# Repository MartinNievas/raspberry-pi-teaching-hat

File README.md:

# raspberry-pi-teaching-hat

## Pinout

## Programa de ejemplo
Un programa de ejemplo se encuentra en la carpeta lib/

Ejecutar:

```bash
gcc ejemplo.c && sudo ./a.out
```
Nota: sudo es necesario para acceder al pinout.

---
Para más información ir a la [Wiki](https://github.com/MartinNievas/raspberry-pi-teaching-hat/wiki)
---

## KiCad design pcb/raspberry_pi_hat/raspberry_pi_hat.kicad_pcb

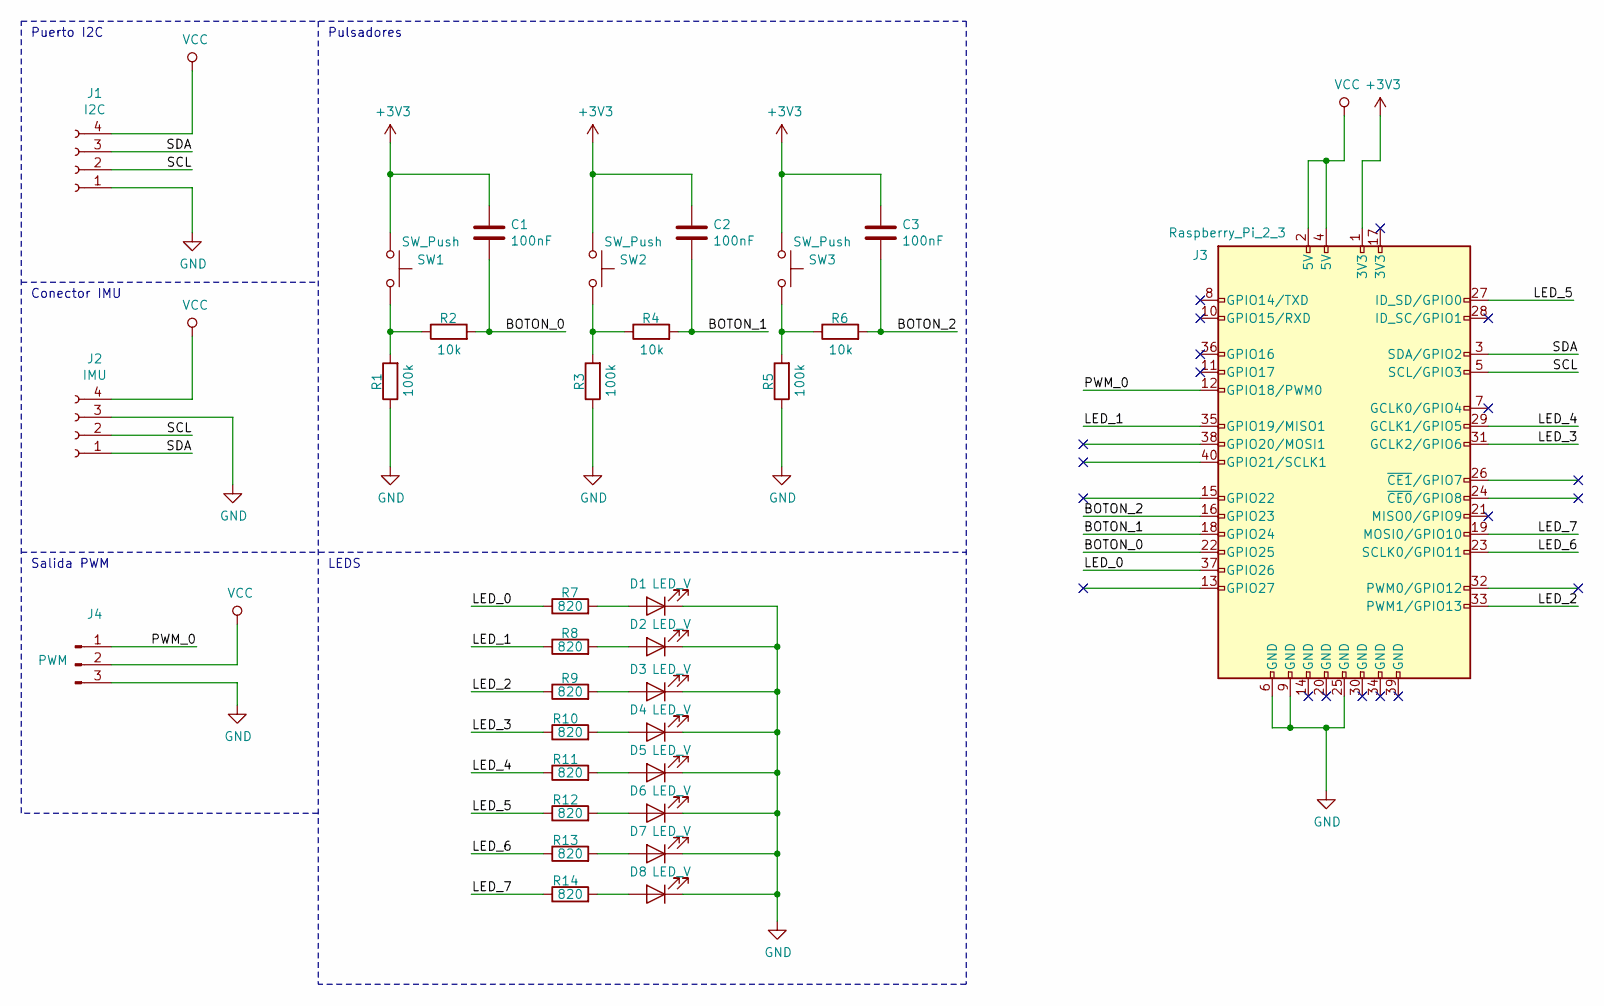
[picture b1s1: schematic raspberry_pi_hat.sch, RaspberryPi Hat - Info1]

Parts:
C1, C2, C3: 100nF; cnp_6mm_disc
D1, D2, D3, D4, D5, D6, D7, D8: LED_V; LED_D5.0mm
J1: I2C; PinHeader_1x04_P2.54mm_Vertical
J2: IMU; PinHeader_1x04_P2.54mm_Vertical
J3: Raspberry_Pi_2_3; Pin_Header_Straight_2x20
J4: PWM; PinHeader_1x03_P2.54mm_Horizontal
R1, R3, R5: 100k; R_BIG_Axial_DIN0207
R2, R4, R6: 10k; R_BIG_Axial_DIN0207
R7, R8, R9, R10, R11, R12, R13, R14: 820; R_BIG_Axial_DIN0207
SW1, SW2, SW3: SW_Push; SW_PUSH_6mm

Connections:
+3V3: C1.1, C2.1, C3.1, J3.1 (3V3), SW1.1, SW2.1, SW3.1
/BOTON_0: C1.2, J3.22 (GPIO25), R2.2
/BOTON_1: C2.2, J3.18 (GPIO24), R4.2
/BOTON_2: C3.2, J3.16 (GPIO23), R6.2
/LED_0: J3.37 (GPIO26), R7.1
/LED_1: J3.35 (GPIO19/MISO1), R8.1
/LED_2: J3.33 (PWM1/GPIO13), R9.1
/LED_3: J3.31 (GCLK2/GPIO6), R10.1
/LED_4: J3.29 (GCLK1/GPIO5), R11.1
/LED_5: J3.27 (ID_SD/GPIO0), R12.1
/LED_6: J3.23 (SCLK0/GPIO11), R13.1
/LED_7: J3.19 (MOSI0/GPIO10), R14.1
/PWM_0: J3.12 (GPIO18/PWM0), J4.1
/SCL: J1.2, J2.2, J3.5 (SCL/GPIO3)
/SDA: J1.3, J2.1, J3.3 (SDA/GPIO2)
GND: D1.1 (K), D2.1 (K), D3.1 (K), D4.1 (K), D5.1 (K), D6.1 (K), D7.1 (K), D8.1 (K), J1.1, J2.3, J3.6 (GND), J3.9 (GND), J3.25 (GND), J4.3, R1.1, R3.1, R5.1
unnamed: D1.2 (A), R7.2
unnamed: D2.2 (A), R8.2
unnamed: D3.2 (A), R9.2
unnamed: D4.2 (A), R10.2
unnamed: D5.2 (A), R11.2
unnamed: D6.2 (A), R12.2
unnamed: D7.2 (A), R13.2
unnamed: D8.2 (A), R14.2
unnamed: R1.2, R2.1, SW1.2
unnamed: R3.2, R4.1, SW2.2
unnamed: R5.2, R6.1, SW3.2
VCC: J1.4, J2.4, J3.2 (5V), J3.4 (5V), J4.2

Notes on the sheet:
Puerto I2C
Conector IMU
Salida PWM
LEDS
Pulsadores

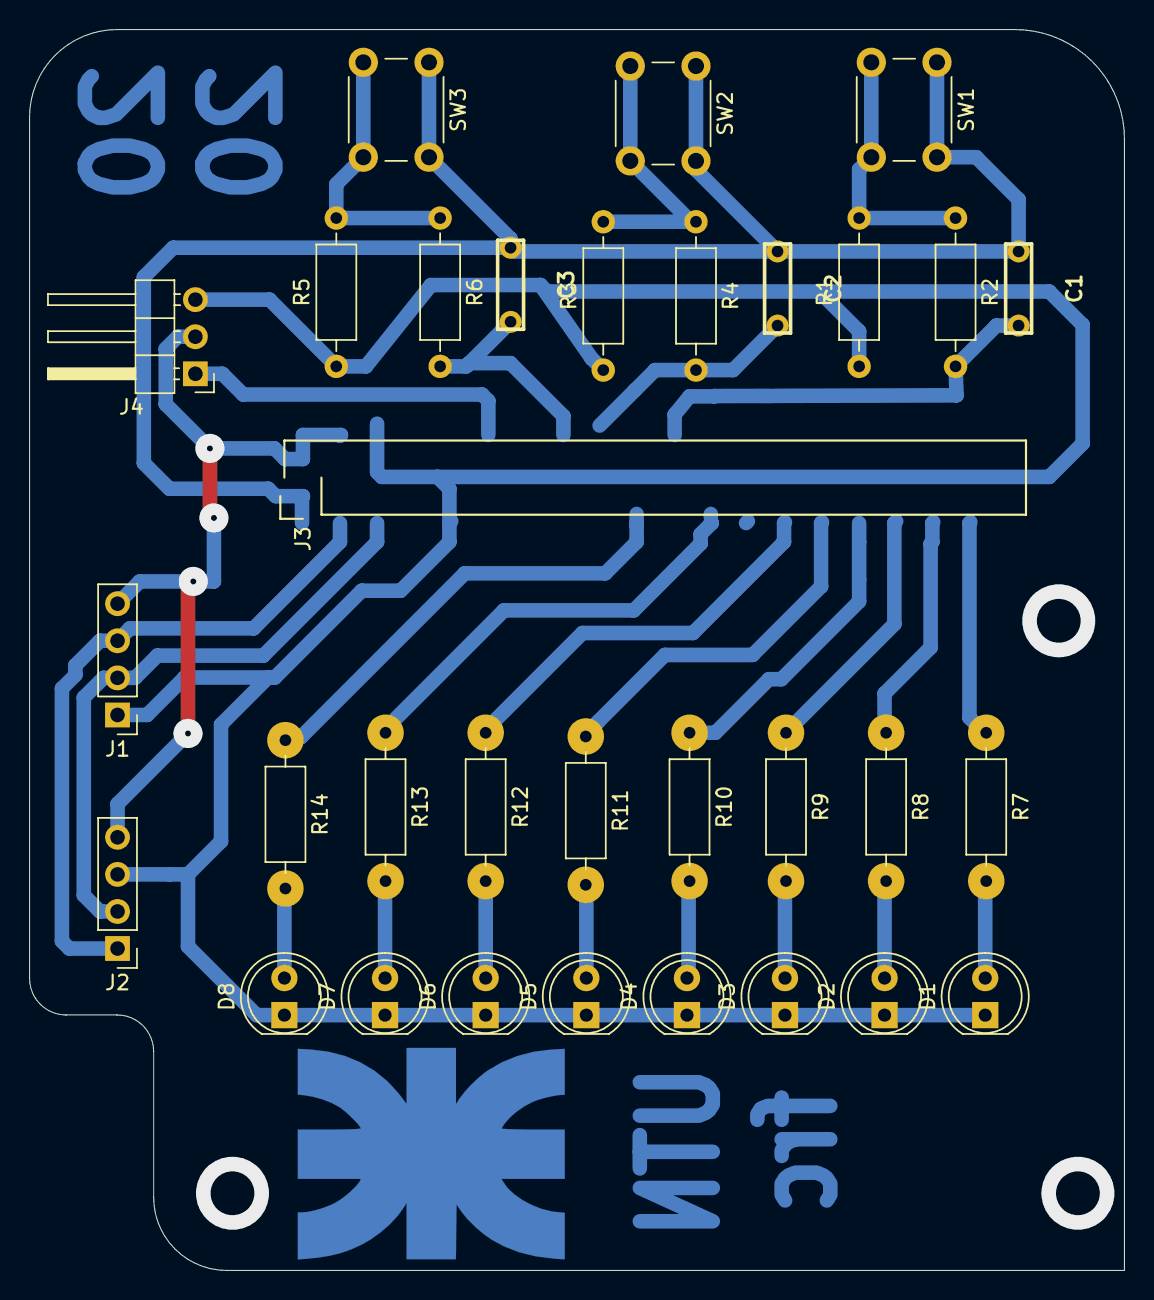
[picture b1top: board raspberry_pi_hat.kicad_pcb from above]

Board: 2 copper layers, 75.0 x 85.0 mm, 32 parts (0 on the bottom side), 28 nets.

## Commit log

2019-07-02 Add gitignore for KiCad files
2020-02-26 Agrega versión 0.1 del hat
2020-02-26 Agrega renders de la placa
2020-02-26 Agrega render al README
2020-03-10 Agrega modificaciones en el tamaño del PCB
2020-03-14 Agrega modelos para el case
2020-03-14 Agrega render de la placa
2020-03-14 Agrega links a los modelos stl
2020-03-14 Agrega imágenes de la placa nueva
2020-03-14 Corrige una esquina del case
2020-03-19 Agrega documentación y pinout
2020-03-19 Agrega biblioteca EasyPIO.h y programa de ejemplo
2020-03-22 Agrega Makefile y ejemplo de la imu
    - Se agrega un makefile para compilar los programas de ejemplo
    - Se agrega un ejemplo para utilizar la IMU MPU6050 conectada a la placa
2020-03-28 Agrega aplicación de ejemplo para manejar PWM
    - Aplicación utilizando la biblioteca EasyPIO
    - Aplicación utilizando la wiringPi
2020-08-25 Agrega link a la wiki
2021-05-02 Agrega recordatorio de utilizar sudo
